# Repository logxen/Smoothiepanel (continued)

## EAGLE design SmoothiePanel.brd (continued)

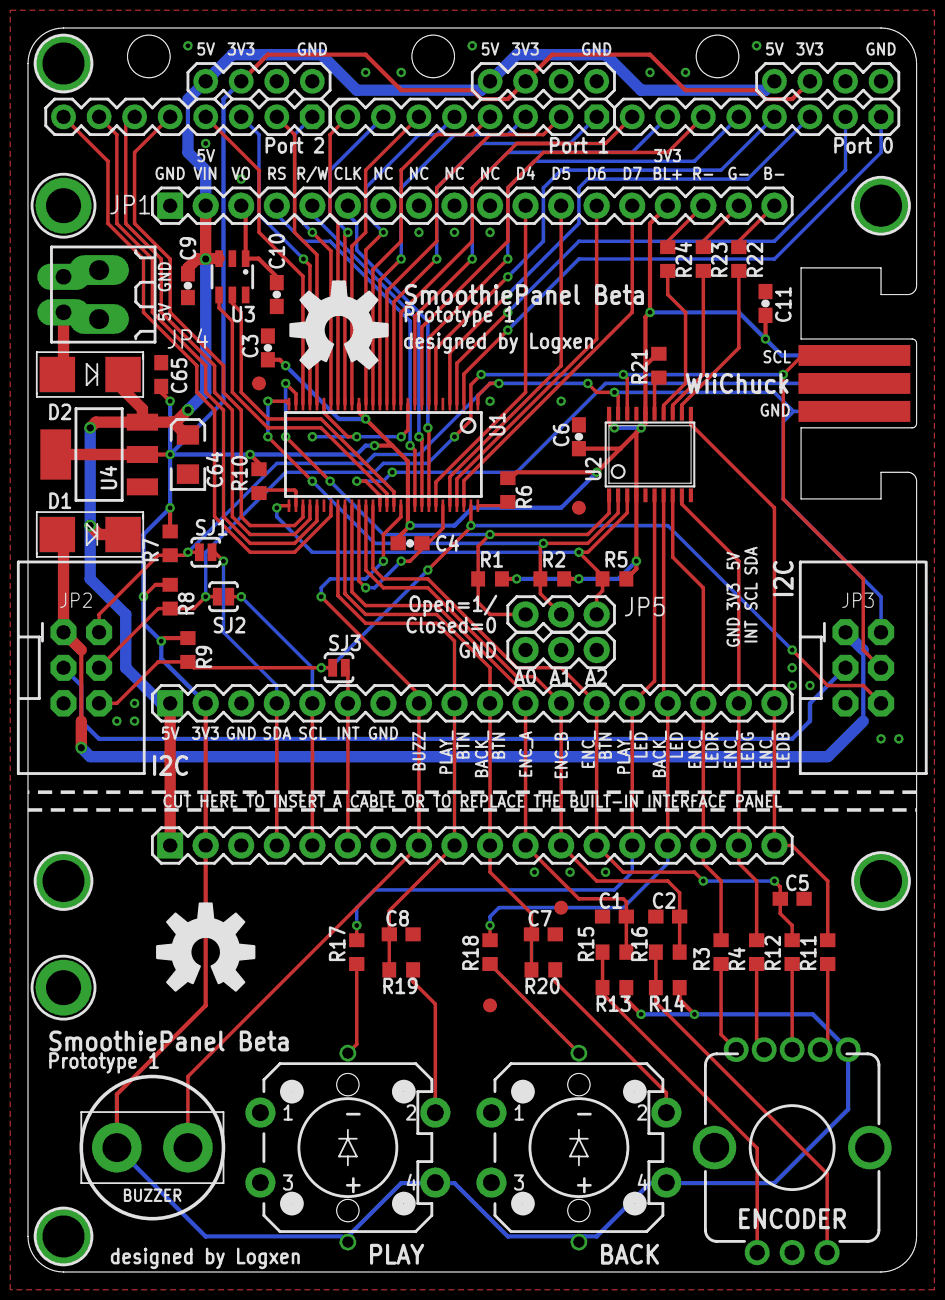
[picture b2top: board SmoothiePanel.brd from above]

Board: 2 copper layers, 63.5 x 88.9 mm, 77 parts (1 on the bottom side), 80 nets.

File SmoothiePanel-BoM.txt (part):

Partlist

Exported from SmoothiePanel.brd at 6/8/2013 3:28:27 AM
Edited by Logxen at 6/16/2013 3:33 PM

EAGLE Version 6.4.0 Copyright (c) 1988-2013 CadSoft

Assembly variant: 

Part     Value                 Package                       Library              Position (inch)       Orientation

C1       0.01uF                C0603                         rcl                  (1.65 1)              R180
C2       0.01uF                C0603                         rcl                  (1.8 1)               R180
C3       0.1uF                 0603-CAP                      SparkFun-Capacitors  (0.675 2.6)           R90
C4       0.1uF                 0603-CAP                      SparkFun-Capacitors  (1.075 2.05)          R0
C5       0.1uF+10K             C0603                         rcl                  (2.15 1.05)           R0
C6       0.1uF                 0603-CAP                      SparkFun-Capacitors  (1.55 2.35)           R90
C7       0.1uF+10K             C0603                         rcl                  (1.45 0.95)           R0
C8       0.1uF+10K             C0603                         rcl                  (1.05 0.95)           R0
C9       0.1uF                 0603-CAP                      SparkFun-Capacitors  (0.45 2.775)          R270
C10      0.1uF                 0603-CAP                      SparkFun-Capacitors  (0.7 2.75)            R270
C11      0.1uF                 0603-CAP                      SparkFun-Capacitors  (2.075 2.725)         R90
C64      10uF                  EIA3216                       SparkFun             (0.45 2.3)            R90
C65      0.1uF                 C0603                         resistor             (0.375 2.525)         R90
D1       MBRA210LT3            SMADIODE                      microbuilder         (0.175 2.075)         R180
D2       MBRA210LT3            SMADIODE                      microbuilder         (0.175 2.525)         R180
R1       10kOhm                R0603                         resistor             (1.3 1.95)            R0
R2       10kOhm                R0603                         resistor             (1.475 1.95)          R0
R3       330 Ohm               R0603                         resistor             (1.95 0.9)            R90
R4       330 Ohm               R0603                         resistor             (2.05 0.9)            R90
R5       10kOhm                R0603                         resistor             (1.65 1.95)           R0
R9       10K                   R0603                         resistor             (0.45 1.75)           R90
R11      330 Ohm               R0603                         resistor             (2.25 0.9)            R90
R12      10kOhm->1.1K          R0603                         resistor             (2.15 0.9)            R90
R13      10kOhm                R0603                         resistor             (1.65 0.8)            R0
R14      10kOhm                R0603                         resistor             (1.8 0.8)             R0
R15      10kOhm                R0603                         resistor             (1.65 0.9)            R0
R16      10kOhm                R0603                         resistor             (1.8 0.9)             R0
R17      330 Ohm               R0603                         resistor             (0.925 0.9)           R90
R18      330 Ohm               R0603                         resistor             (1.3 0.9)             R90
R19      10kOhm->1.1K          R0603                         resistor             (1.05 0.85)           R180
R20      10kOhm->1.1K          R0603                         resistor             (1.45 0.85)           R180
R21      10kOhm                R0603                         resistor             (1.775 2.55)          R90
R22      330 Ohm               R0603                         resistor             (2 2.85)              R270
R23      330 Ohm               R0603                         resistor             (1.9 2.85)            R270
R24      330 Ohm               R0603                         resistor             (1.8 2.85)            R270
U1       PCA9505               TSSOP56-6                     micro-philips        (1 2.3)               R180
U2       PCA9634-TSSOP20       TSSOP20                       logxen               (1.75 2.3)            R0
U3       MCP4725               SOT23-6                       microbuilder         (0.575 2.8)           R180
U4       LM1117-3.3V           SOT223                        SparkFun             (0.2 2.3)             R90

JP1      20x4 RGB CHAR_LCD     1X18-FEMALE                   logxen               (0.4 3)               R0
JP2      I2C                   2X3-SHROUDED-90D              SparkFun-Connectors  (0.15 1.7)            R0
JP5      ADDRESS               1X03                          SparkFun-Connectors  (1.4 1.85)            R0
JP13     ADDRESS_GND           1X03                          SparkFun-Connectors  (1.4 1.75)            R0

JP10     BUZZ                  1X02_XTRA_BIG                 SparkFun-Connectors  (0.35 0.35)           R0
SW1      ENCODER               ENCODER_LED_3                 SparkFun             (2.15 0.35)           R0
SW2      BACK                  TACTILE-PTH-LED-12MM          Local Library        (1.55 0.35)           R0
SW3      PLAY/PAUSE            TACTILE-PTH-LED-12MM          Local Library        (0.9 0.35)            R0

JP3      I2C                   2X3-SHROUDED-90D              SparkFun-Connectors  (2.35 1.7)            R0
JP4      PWR                   1X02_LONGPADS                 SparkFun-Connectors  (0.1 2.7)             R90
X1       PWR                   180-2                         con-weidmueller-sl35 (0.2 2.75)            R90
U$2      PAPILIO-WING-8BITS    PAPILIO-WING-8BITS            logxen               (2.4 3.25)            R90
U$3      PAPILIO-WING-8BITS    PAPILIO-WING-8BITS            logxen               (1.6 3.25)            R90
U$4      PAPILIO-WING-8BITS    PAPILIO-WING-8BITS            logxen               (0.8 3.25)            R90

R6       NP                    R0603                         resistor             (1.35 2.2)            R90
R7       NP                    R0603                         resistor             (0.4 2.05)            R90
R8       NP                    R0603                         resistor             (0.4 1.9)             R90
R10      NP                    R0603                         resistor             (0.65 2.225)          R90
JP8      WII_NUNCHUCK          WII_NUNCHUCK                  logxen               (2.5 2.5)             R180
JP9      FIDUCIAL1X2           FIDUCIAL-1X2                  SparkFun             (1.3 0.75)            R0
JP11     FIDUCIAL1X2           FIDUCIAL-1X2                  SparkFun             (1.55 2.15)           R0
JP12     FIDUCIAL1X2           FIDUCIAL-1X2                  SparkFun             (1.5 1.025)           R0
JP14     FIDUCIAL1X2           FIDUCIAL-1X2                  SparkFun             (0.65 2.5)            R0
SJ1      SDA                   SJ_2S-NO                      SparkFun-Passives    (0.5 2.025)           R0
SJ2      SCL                   SJ_2S-NO                      SparkFun-Passives    (0.55 1.9)            R0
SJ3      INT                   SJ_2S-NO                      SparkFun-Passives    (0.875 1.7)           R0
U$5      MOUNTINGHOLE3.0THIN   MOUNTINGHOLE_3.0_PLATEDTHIN   microbuilder         (2.4 3)               R0
U$6      MOUNTINGHOLE2.5_THICK MOUNTINGHOLE_2.5_PLATED_THICK microbuilder         (0.1 0.8)             R0
U$7      MOUNTINGHOLE2.5_THICK MOUNTINGHOLE_2.5_PLATED_THICK microbuilder         (0.1 3)               R0
U$9      MOUNTINGHOLE3.0THIN   MOUNTINGHOLE_3.0_PLATEDTHIN   microbuilder         (0.1 1.1)             R0
U$11     M18_                  1X18                          SparkFun-Connectors  (0.4 1.6)             R0
U$12     M18_                  1X18                          SparkFun-Connectors  (0.4 1.2)             R0
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
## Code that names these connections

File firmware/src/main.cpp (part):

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        case 0x10: // write lcd data byte
            lcd_d.output();
            lcd_d = d;
            lcd_rs = 1; // 0 cmd, 1 dat
            lcd_rw = 0; // 0 write, 1 read
            lcd_en = 0;
            wait(0.01);
            lcd_en = 1;
            wait(0.01);
            lcd_en = 0;
            r = 0x1000 + d;
            break;
        case 0x11: // read lcd data byte
            lcd_d.input();
            lcd_rs = 1; // 0 cmd, 1 dat
            lcd_rw = 1; // 0 write, 1 read
            lcd_en = 0;
            wait(0.01);
            lcd_en = 1;
            wait(0.01);
            r = 0x1100 + lcd_d;
            lcd_en = 0;
            break;
        case 0x12: // write lcd command byte
            lcd_d.output();
            lcd_d = d;
            lcd_rs = 0; // 0 cmd, 1 dat
            lcd_rw = 0; // 0 write, 1 read
            lcd_en = 0;
            wait(0.01);
            lcd_en = 1;
            wait(0.01);
            lcd_en = 0;
            r = 0x1200 + d;
            break;
        case 0x13: // read lcd command byte
            lcd_d.input();
            lcd_rs = 0; // 0 cmd, 1 dat
            lcd_rw = 1; // 0 write, 1 read
            lcd_en = 0;
            wait(0.01);
            lcd_en = 1;
            wait(0.01);
            r = 0x1300 + lcd_d;
            lcd_en = 0;
            break;
        case 0x14: // reset lcd
            lcd_rst = 1;
            wait(0.01);
            lcd_rst = 0;
            r = 0x1400 + d;
            break;

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    init_gpio();

    lcd_d.input();
    lcd_rs = 0; // 0 cmd, 1 dat
    lcd_rw = 0; // 0 write, 1 read
    lcd_en = 0;
    lcd_psb = 1; // 0 serial, 1 parallel
    lcd_rst = 0;
    wait(0.01);
    lcd_rst = 1;
    wait(0.01);
    lcd_rst = 0;

    spimaster.format(8,0);
    spimaster.frequency(1000000);
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
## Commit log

2013-07-01 Initial commit (Prototype 1)
2014-02-09 Initial commit (Prototype 3)
    Includes hardware and firmware source
2014-02-09 Added flashing to readme
2014-02-09 Added note about win dragndrop flashing to readme
2014-02-09 Improved instructions for building the firmware
2014-02-10 Added openmoko usb vid/pid 0x1D50/0x60A0
2014-02-10 Added windows driver for usb serial
2014-02-11 added encoder module
2014-02-11 added commands to retrieve usb id and version info
2014-08-15 Initial hardware commit (Prototype 5)
